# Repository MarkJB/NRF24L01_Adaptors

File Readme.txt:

NRF24L01 adaptor boards for Raspberry Pi, Arduino Uno, Leonardo and Nano.

Copyright Mark Benson 2018

I've updated the Nano board licence to Creative Attribution-ShareAlike 4.0 International (CC BY-SA 4.0)

All others in this repo are still at License: Creative Commons Attribution Non Commerical 4.0 (CCBYNC 4.0)

See the Wiki for assembly instructions.

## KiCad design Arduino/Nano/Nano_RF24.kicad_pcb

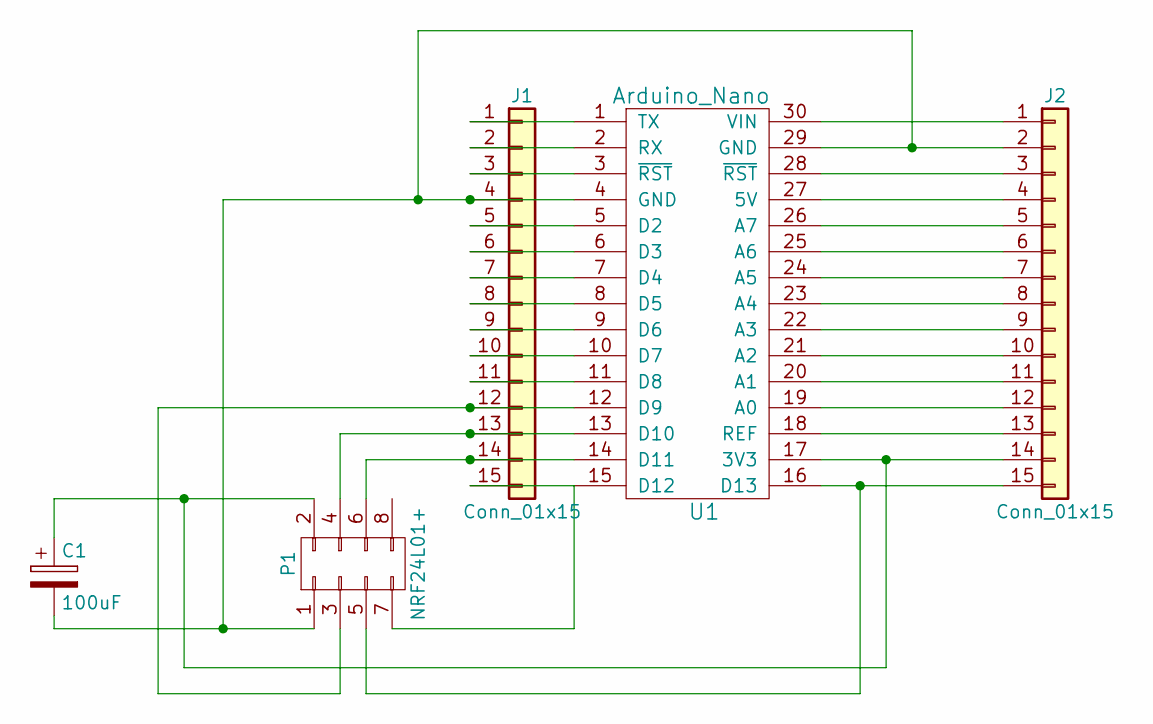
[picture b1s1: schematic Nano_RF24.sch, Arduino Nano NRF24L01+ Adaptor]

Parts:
C1: 100uF; C_Radial_D5_L11_P2.5
J1, J2: Conn_01x15; Pin_Header_Straight_1x15_Pitch2.54mm
P1: NRF24L01+
U1: Arduino_Nano; Arduino_nano_v3

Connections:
unnamed: C1.1, J2.14, P1.2, U1.17 (3V3)
unnamed: C1.2, J1.4, J2.2, P1.1, U1.4 (GND), U1.29 (GND)
unnamed: J1.1, U1.1 (TX)
unnamed: J1.2, U1.2 (RX)
unnamed: J1.3, U1.3 (~RST)
unnamed: J1.5, U1.5 (D2)
unnamed: J1.6, U1.6 (D3)
unnamed: J1.7, U1.7 (D4)
unnamed: J1.8, U1.8 (D5)
unnamed: J1.9, U1.9 (D6)
unnamed: J1.10, U1.10 (D7)
unnamed: J1.11, U1.11 (D8)
unnamed: J1.12, P1.3, U1.12 (D9)
unnamed: J1.13, P1.4, U1.13 (D10)
unnamed: J1.14, P1.6, U1.14 (D11)
unnamed: J1.15, P1.7, U1.15 (D12)
unnamed: J2.1, U1.30 (VIN)
unnamed: J2.3, U1.28 (~RST)
unnamed: J2.4, U1.27 (5V)
unnamed: J2.5, U1.26 (A7)
unnamed: J2.6, U1.25 (A6)
unnamed: J2.7, U1.24 (A5)
unnamed: J2.8, U1.23 (A4)
unnamed: J2.9, U1.22 (A3)
unnamed: J2.10, U1.21 (A2)
unnamed: J2.11, U1.20 (A1)
unnamed: J2.12, U1.19 (A0)
unnamed: J2.13, U1.18 (REF)
unnamed: J2.15, P1.5, U1.16 (D13)

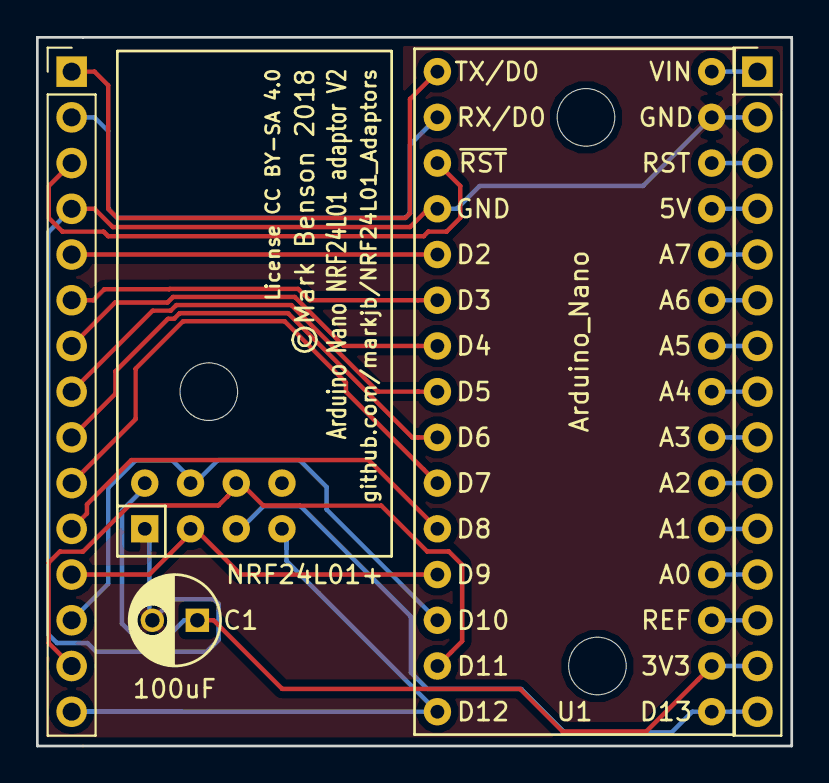
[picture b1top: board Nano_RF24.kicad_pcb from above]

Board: 2 copper layers, 41.9 x 39.4 mm, 5 parts (0 on the bottom side), 29 nets.

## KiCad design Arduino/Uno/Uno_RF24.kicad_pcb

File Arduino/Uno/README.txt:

Arduino Shield footprints available from https://github.com/freetronics/freetronics_kicad_library

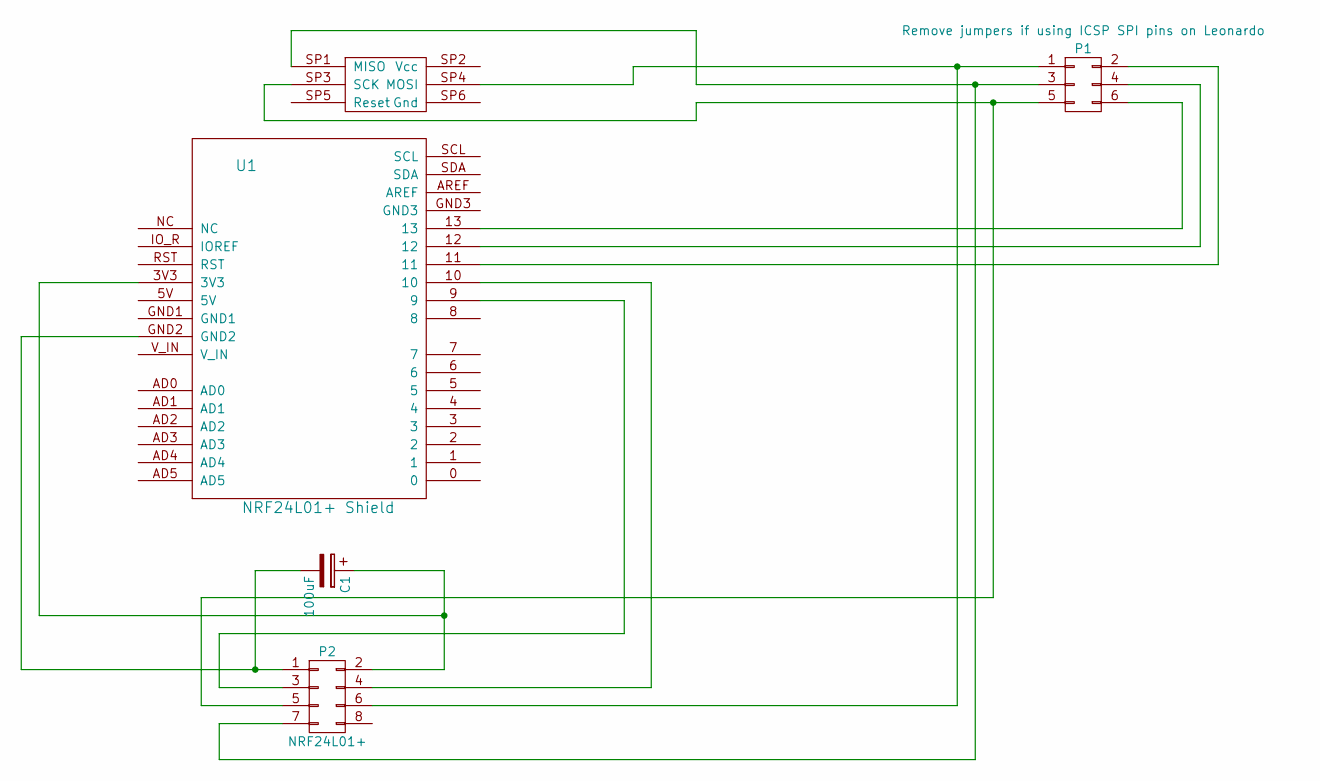
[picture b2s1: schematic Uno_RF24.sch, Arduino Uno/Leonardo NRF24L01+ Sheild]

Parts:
C1: 100uF; C_Radial_D5_L11_P2.5
P1: Remove jumpers if using ICSP SPI pins on Leonardo; Pin_Header_Straight_2x03
P2: NRF24L01+
U1: NRF24L01+ Shield; ARDUINO_SHIELD_ROUNDPADS

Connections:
unnamed: C1.1, P2.2, U1.3V3
unnamed: C1.2, P2.1, U1.GND2
unnamed: P1.1, P2.6, U1.SP4 (MOSI)
unnamed: P1.2, U1.11
unnamed: P1.3, P2.7, U1.SP1 (MISO)
unnamed: P1.4, U1.12
unnamed: P1.5, P2.5, U1.SP3 (SCK)
unnamed: P1.6, U1.13
unnamed: P2.3, U1.9
unnamed: P2.4, U1.10

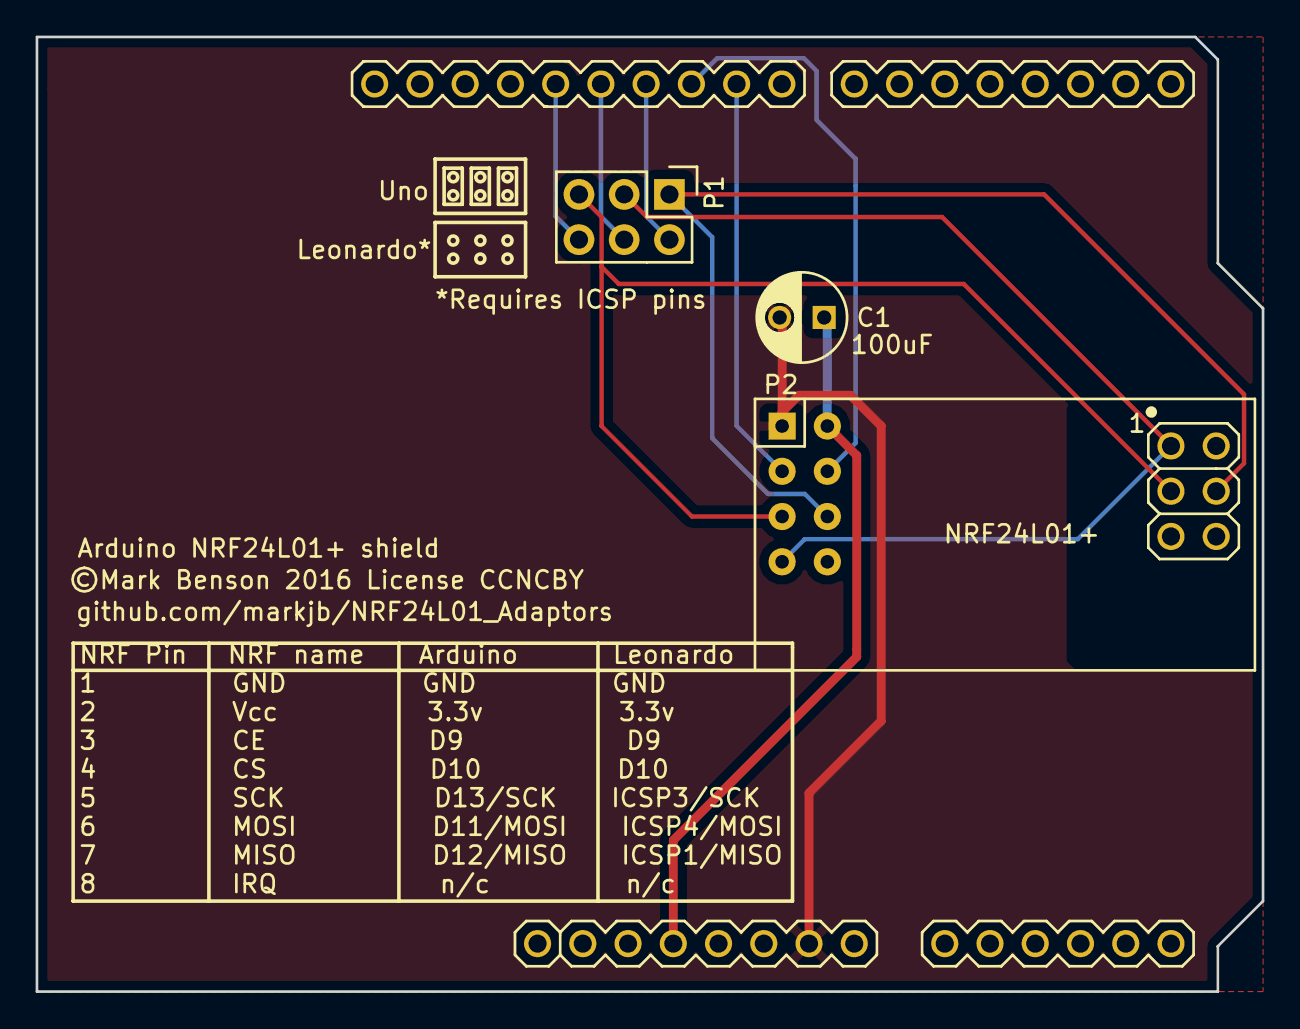
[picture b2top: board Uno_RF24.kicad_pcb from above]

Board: 2 copper layers, 68.8 x 53.6 mm, 4 parts (0 on the bottom side), 10 nets.

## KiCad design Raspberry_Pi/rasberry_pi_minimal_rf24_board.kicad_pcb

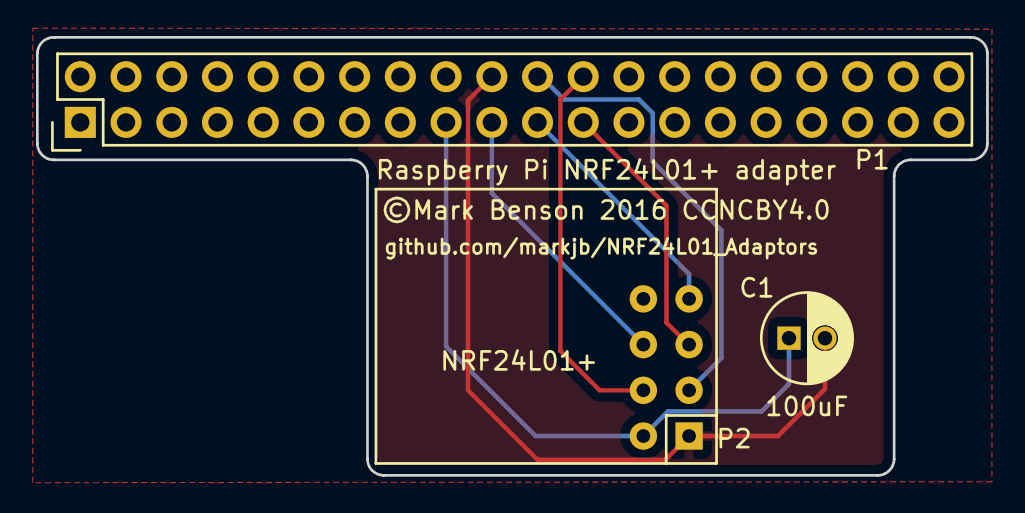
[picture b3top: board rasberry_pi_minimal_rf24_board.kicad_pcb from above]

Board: 2 copper layers, 52.8 x 24.3 mm, 3 parts (0 on the bottom side), 7 nets.

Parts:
C1: 100uF; C_Radial_D5_L11_P2
P1: RPi; Pin_Header_Straight_2x20
P2: NRF24L01+; NRF24L01+_short

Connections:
unnamed: C1.1, P1.17, P2.2
unnamed: C1.2, P1.20, P2.1
unnamed: P1.19, P2.6
unnamed: P1.21, P2.7
unnamed: P1.22, P2.3
unnamed: P1.23, P2.5
unnamed: P1.24, P2.4

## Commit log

2016-08-15 :confetti_ball: Added .gitattributes & .gitignore files
2016-08-15 footprint readm
2016-08-15 Update URLs and images
2018-03-30 Updated licence and copyright
2018-03-30 v2 with breakout pins
2018-03-30 Updated png
2020-12-22 Add pictures

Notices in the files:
Arduino/Nano/Nano_RF24.kicad_pcb:
License Creative Commons Attribution ShareAlike 4.0 (CC BY-SA 4.0)
License CC BY-SA 4.0
©Mark Benson 2018
Arduino/Uno/Uno_RF24.kicad_pcb:
Copyright Mark Benson 2016
License: Creative Commons Attribution Non Commercial (CCNCBY 4.0)
©Mark Benson 2016 License CCNCBY
Raspberry_Pi/rasberry_pi_minimal_rf24_board.kicad_pcb:
License: Creative Commons Attribution Non Commerical 4.0 (CCNCBY 4.0)
©Mark Benson 2016 CCNCBY4.0
